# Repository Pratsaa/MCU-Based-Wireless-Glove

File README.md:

# MCU-Based Wireless Glove  

This project is a **wireless gesture-controlled glove** that streams **finger bends (flex sensors)** and **palm motion (IMU)** to a PC, where a Unity application animates a virtual hand in real time.  
- **STM32L031 MCU**: samples and processes sensor data.  
- **ESP32-WROOM**: handles wireless transmission via ESP-NOW.  
- **Python bridge**: ingests and calibrates data, then forwards it to Unity.  
- **Unity C# script**: applies finger and palm movements to a 3D hand model.  

👉 For detailed technical documentation (hardware schematics, PCB design, and system explanation), please see the [Docs/](./Docs) folder.  

---

## 📂 Repository Structure  

MCU-Based-Wireless-Glove/
│
├── Docs/ # Project documentation (ECE395 Final Report + notes)
├── pcb-files/ # PCB schematics, layouts, and related design files
├── src/ # Source code for firmware, PC bridge, and Unity listener
│ ├── stm32/ # STM32 firmware (ADC, IMU SPI, UART output)
│ ├── esp32/ # ESP32 firmware (ESP-NOW wireless bridge, optional IMU polling)
│ ├── python/ # PC-side scripts (serial ingest, calibration, TCP forward)
│ └── unity/ # Unity C# listener scripts (GloveReceiver.cs)
├── placeholder/ # Temporary / unused files (safe to ignore)
├── LICENSE # License information
└── README.md # Project overview (this file)

- **Docs/** – contains the final project report and supporting documents. Start here if you want to understand the full design.  
- **pcb-files/** – all hardware-related design files for the custom PCB.  
- **src/** – source code divided into:  
  - **stm32/** – firmware for STM32L031 MCU (flex sensor ADC, IMU via SPI, UART data framing).  
  - **esp32/** – firmware for ESP32 (wireless data forwarding using ESP-NOW, with optional IMU fallback).  
  - **python/** – PC bridge (`main.py` and helpers) that parses UART data, calibrates sensor values, and forwards JSON over TCP.  
  - **unity/** – Unity scripts (e.g., `GloveReceiver.cs`) that apply incoming data to animate a 3D hand model.  
- **placeholder/** – unused or staging area, not critical to the project.  

---

## ▶️ How It Works  

1. **Sensor acquisition**  
   - Flex sensors + op-amp circuits measure finger bends.  
   - IMU (ICM-20948) provides palm orientation and motion data.  
   - STM32 samples all signals and sends data over UART to the ESP32.  

2. **Wireless bridge**  
   - ESP32 transmits processed sensor data wirelessly to the PC via ESP-NOW.  

3. **PC bridge (Python)**  
   - Parses UART data, calibrates values, and forwards JSON packets over TCP.  

4. **Unity listener**  
   - Receives the data and animates a virtual hand in Unity with low latency.  

---

## 🛠️ Getting Started  

- Build and flash STM32 firmware (inside `src/`).  
- Flash ESP32 firmware (inside `src/`).  
- Run the Python script to ingest sensor data and forward to Unity.  
- Import the Unity C# script into your project to animate the hand.  

**Dependencies:**  
- STM32CubeIDE (or equivalent toolchain)  
- ESP-IDF for ESP32  
- Python 3.x with `pyserial`  
- Unity (2021 LTS or newer recommended)  

---

## 📖 Documentation  

Full documentation and project report can be found in [Docs/](./Docs). This includes:  
- Hardware schematics & PCB design decisions  
- Firmware architecture  
- Python/Unity pipeline  
- Performance metrics and improvements  

---

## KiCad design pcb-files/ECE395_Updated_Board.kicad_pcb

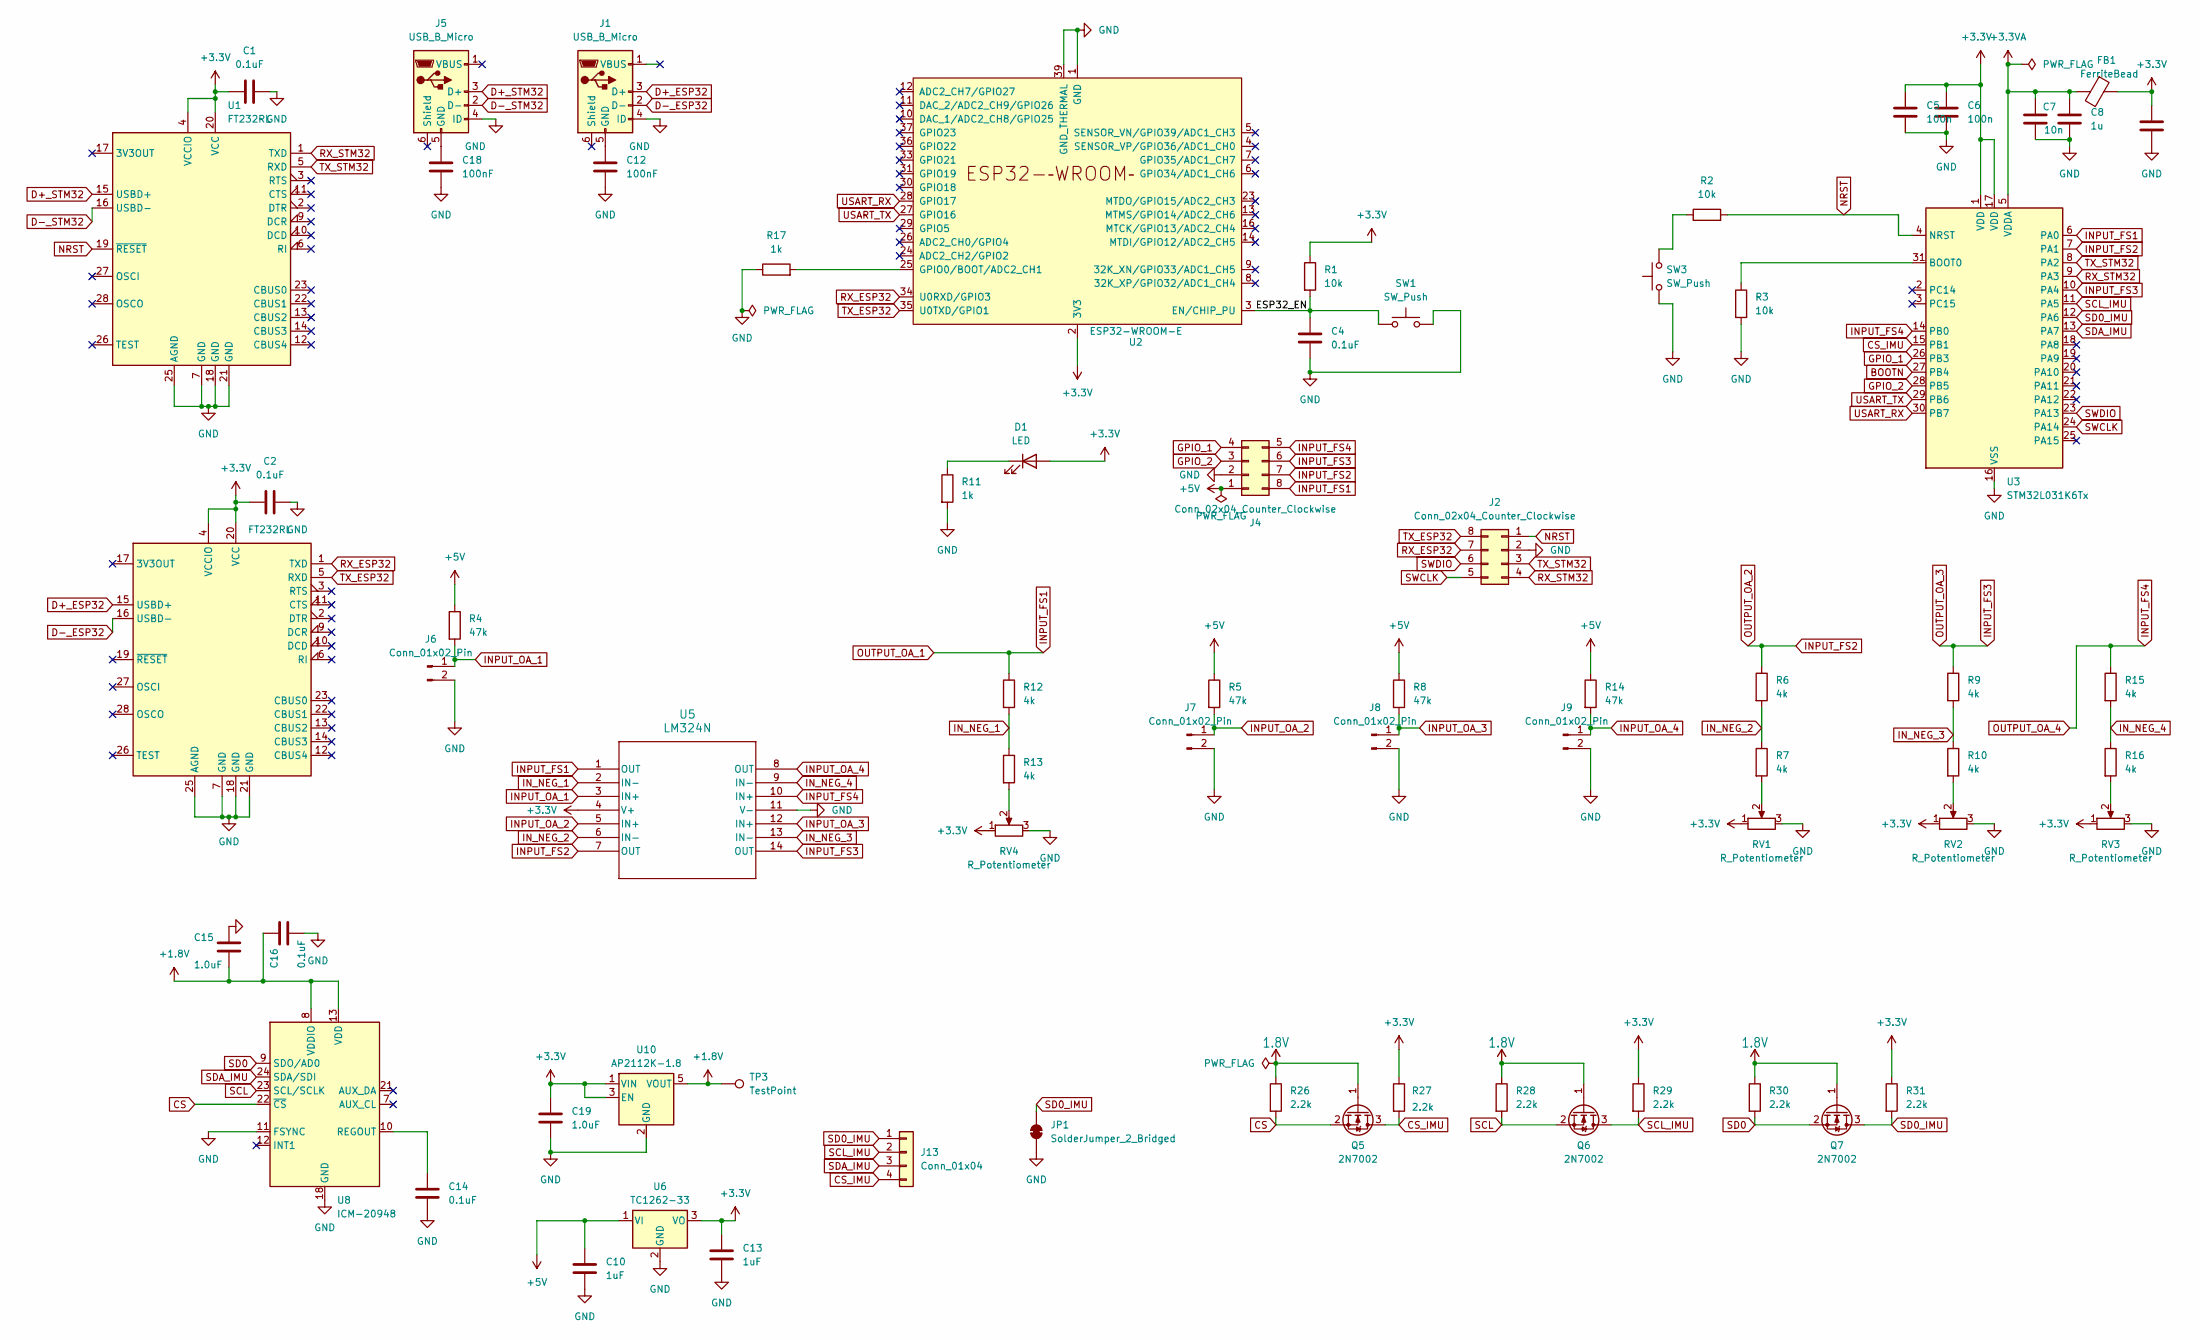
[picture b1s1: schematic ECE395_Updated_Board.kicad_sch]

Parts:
C1, C2, C4, C14, C16: 0.1uF; C_0805_2012Metric_Pad1.18x1.45mm_HandSolder
C5, C6: 100n; C_0805_2012Metric_Pad1.18x1.45mm_HandSolder
C7: 10n; C_0805_2012Metric_Pad1.18x1.45mm_HandSolder
C8, C9: 1u; C_0805_2012Metric_Pad1.18x1.45mm_HandSolder
C10, C13: 1uF; C_0805_2012Metric_Pad1.18x1.45mm_HandSolder
C12, C18: 100nF; C_0805_2012Metric_Pad1.18x1.45mm_HandSolder
C15, C19: 1.0uF; C_0805_2012Metric_Pad1.18x1.45mm_HandSolder
D1: LED; LED_0805_2012Metric_Pad1.15x1.40mm_HandSolder
FB1: FerriteBead; L_0805_2012Metric_Pad1.15x1.40mm_HandSolder
J1, J5: USB_B_Micro; USB_Micro-B_Amphenol_10118194-0001LF_Horizontal
J2, J4: Conn_02x04_Counter_Clockwise; PinHeader_2x04_P2.54mm_Vertical
J6, J7, J8, J9: Conn_01x02_Pin; PinHeader_1x02_P2.54mm_Vertical
J13: Conn_01x04; PinHeader_1x04_P2.54mm_Vertical
JP1: SolderJumper_2_Bridged; SolderJumper-2_P1.3mm_Bridged_RoundedPad1.0x1.5mm
Q5, Q6, Q7: 2N7002; SOT-23
R1, R2, R3: 10k; R_0805_2012Metric_Pad1.20x1.40mm_HandSolder
R4, R5, R8, R14: 47k; R_0805_2012Metric_Pad1.20x1.40mm_HandSolder
R6, R7, R9, R10, R12, R13, R15, R16: 4k; R_0805_2012Metric_Pad1.20x1.40mm_HandSolder
R11, R17: 1k; R_0805_2012Metric_Pad1.20x1.40mm_HandSolder
R26, R27, R28, R29, R30, R31: 2.2k; R_0805_2012Metric_Pad1.20x1.40mm_HandSolder
RV1, RV2, RV3, RV4: R_Potentiometer; Potentiometer_Bourns_3296W_Vertical
SW1, SW3: SW_Push; SW_PUSH_6mm
TP3: TestPoint; TestPoint_2Pads_Pitch2.54mm_Drill0.8mm
U1, U4: FT232RL; SSOP-28_5.3x10.2mm_P0.65mm
U2: ESP32-WROOM-E; ESP32­WROOM­32E_EXP
U3: STM32L031K6Tx; LQFP-32_7x7mm_P0.8mm
U5: LM324N; DIP-14_STM
U6: TC1262-33; SOT-223
U8: ICM-20948; InvenSense_QFN-24_3x3mm_P0.4mm
U10: AP2112K-1.8; SOT-23-5

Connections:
1.8V: Q5.1 (G), Q6.1 (G), Q7.1 (G), R26.1, R28.1, R30.1
+1.8V: C15.2, C16.1, TP3.1, U8.8 (VDDIO), U8.13 (VDD), U10.5 (VOUT)
+3.3V: C1.1, C2.1, C5.1, C6.1, C9.1, C13.2, C19.1, D1.2 (A), FB1.1, R1.1, R27.1, R29.1, R31.1, RV1.1, RV2.1, RV3.1, RV4.1, U1.4 (VCCIO), U1.20 (VCC), U2.2 (3V3), U3.1 (VDD), U3.17 (VDD), U4.4 (VCCIO), U4.20 (VCC), U5.4 (V+), U6.3 (VO), U10.1 (VIN), U10.3 (EN); also elsewhere on the board
+3.3VA: C7.1, C8.1, FB1.2, U3.5 (VDDA)
+5V: C10.2, J4.1, R4.1, R5.1, R8.1, R14.1, U6.1 (VI)
/ESP32_EN: C4.1, R1.2, SW1.1, U2.3 (EN/CHIP_PU)
BOOTN: U3.27 (PB4)
CS: Q5.2 (S), R26.2, U8.22 (~CS)
CS_IMU: J13.4, Q5.3 (D), R27.2, U3.15 (PB1)
D+_ESP32: J1.3 (D+), U4.15 (USBD+)
D+_STM32: J5.3 (D+), U1.15 (USBD+)
D-_ESP32: J1.2 (D-), U4.16 (USBD-)
D-_STM32: J5.2 (D-), U1.16 (USBD-)
GND: C1.2, C2.2, C4.2, C5.2, C6.2, C7.2, C8.2, C9.2, C10.1, C12.2, C13.1, C14.2, C15.1, C16.2, C18.2, C19.2, J1.4 (ID), J2.2, J4.2, J5.4 (ID), J6.2, J7.2, J8.2, J9.2, JP1.1 (A), R3.2, R11.2, R17.1, RV1.3, RV2.3, RV3.3, RV4.3, SW1.2, SW3.1, U1.7 (GND), U1.18 (GND), U1.21 (GND), U1.25 (AGND), U2.1 (GND), U2.15 (GND), U2.38 (GND), U2.39 (GND_THERMAL), U3.16 (VSS), U3.32 (VSS), U4.7 (GND), U4.18 (GND), U4.21 (GND), U4.25 (AGND), U5.11 (V-), U6.2 (GND), U8.11 (FSYNC), U8.18 (GND), U8.20 (GND), U10.2 (GND)
GPIO_1: J4.4, U3.26 (PB3)
GPIO_2: J4.3, U3.28 (PB5)
INPUT_FS1: J4.8, R12.1, U3.6 (PA0), U5.1 (OUT)
INPUT_FS2: J4.7, R6.1, U3.7 (PA1), U5.7 (OUT)
INPUT_FS3: J4.6, R9.1, U3.10 (PA4), U5.14 (OUT)
INPUT_FS4: J4.5, R15.1, U3.14 (PB0), U5.10 (IN+)
INPUT_OA_1: J6.1, R4.2, U5.3 (IN+)
INPUT_OA_2: J7.1, R5.2, U5.5 (IN+)
INPUT_OA_3: J8.1, R8.2, U5.12 (IN+)
INPUT_OA_4: J9.1, R14.2, U5.8 (OUT)
IN_NEG_1: R12.2, R13.1, U5.2 (IN-)
IN_NEG_2: R6.2, R7.1, U5.6 (IN-)
IN_NEG_3: R9.2, R10.1, U5.13 (IN-)
IN_NEG_4: R15.2, R16.1, U5.9 (IN-)
NRST: J2.1, R2.2, U1.19 (~RESET), U3.4 (NRST)
unnamed: D1.1 (K), R11.1
unnamed: C12.1, J1.5 (GND)
unnamed: C18.1, J5.5 (GND)
unnamed: R2.1, SW3.2
unnamed: R7.2, RV1.2
unnamed: R10.2, RV2.2
unnamed: R13.2, RV4.2
unnamed: R16.2, RV3.2
unnamed 37: R17.2, U2.25 (GPIO0/BOOT/ADC2_CH1); also elsewhere on the board
unnamed: R3.1, U3.31 (BOOT0)
unnamed: C14.1, U8.10 (REGOUT)
RX_ESP32: J2.7, U2.34 (U0RXD/GPIO3), U4.1 (TXD)
RX_STM32: J2.4, U1.1 (TXD), U3.9 (PA3)
SCL: Q6.2 (S), R28.2, U8.23 (SCL/SCLK)
SCL_IMU: J13.2, Q6.3 (D), R29.2, U3.11 (PA5)
SD0: Q7.2 (S), R30.2, U8.9 (SDO/AD0)
SD0_IMU: J13.1, JP1.2 (B), Q7.3 (D), R31.2, U3.12 (PA6)
SDA_IMU: J13.3, U3.13 (PA7), U8.24 (SDA/SDI)
SWCLK: J2.5, U3.24 (PA14)
SWDIO: J2.6, U3.23 (PA13)
TX_ESP32: J2.8, U2.35 (U0TXD/GPIO1), U4.5 (RXD)
TX_STM32: J2.3, U1.5 (RXD), U3.8 (PA2)
USART_RX: U2.28 (GPIO17), U3.30 (PB7)
USART_TX: U2.27 (GPIO16), U3.29 (PB6)

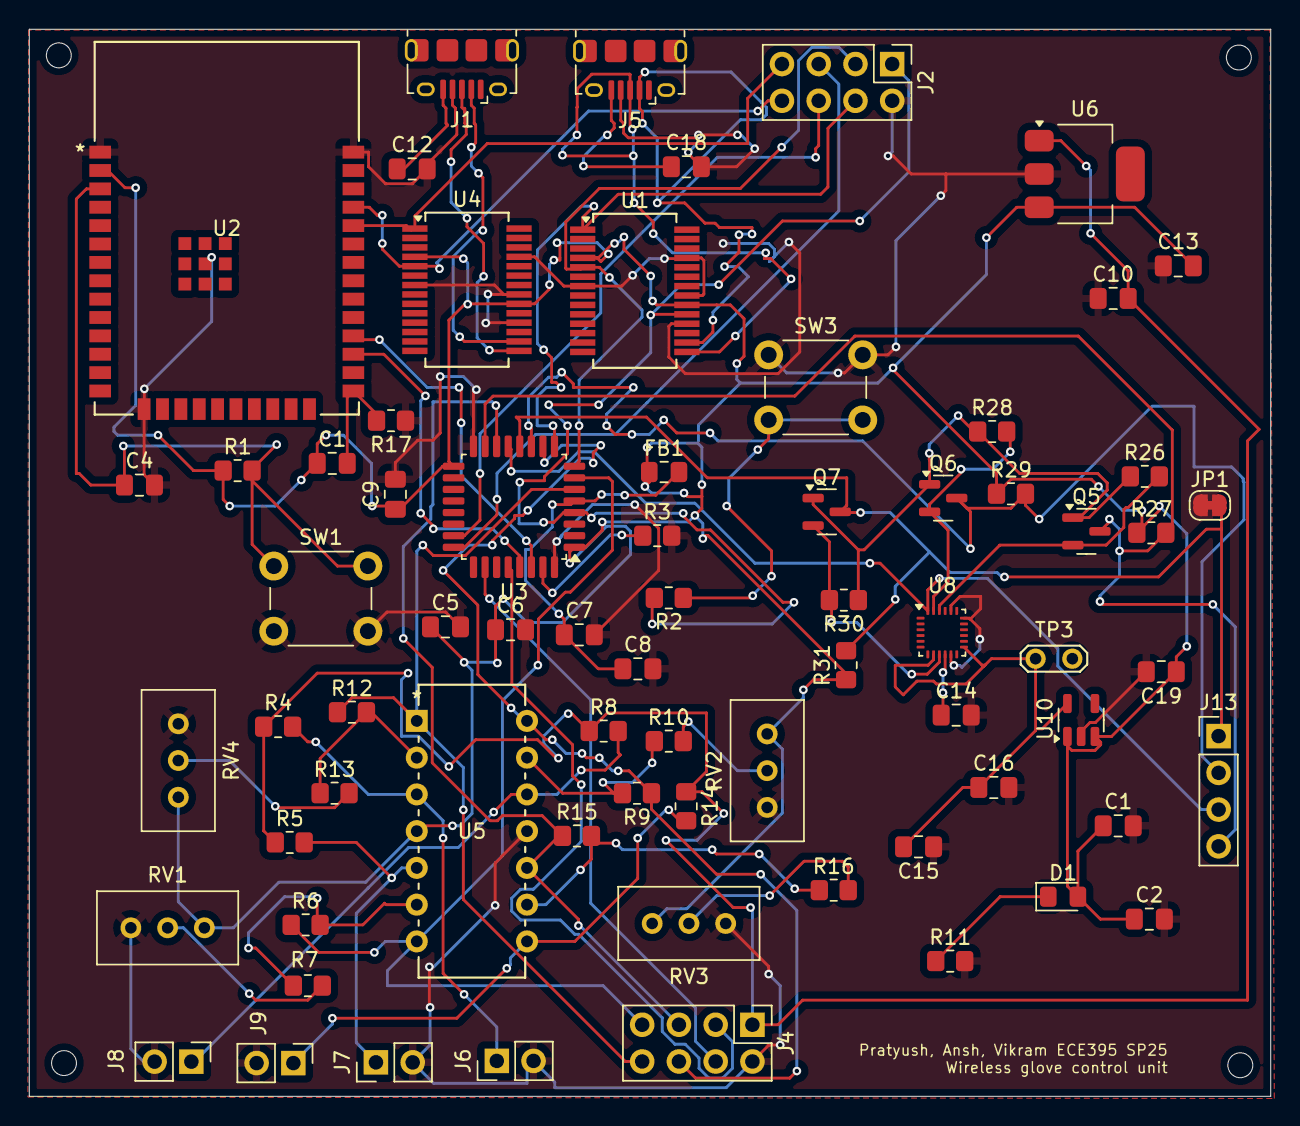
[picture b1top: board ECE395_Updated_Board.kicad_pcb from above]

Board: 2 copper layers, 85.8 x 73.8 mm, 70 parts (0 on the bottom side), 52 nets.

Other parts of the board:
C1#2: 0.1uF; C_0805_2012Metric_Pad1.18x1.45mm_HandSolder

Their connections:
+3.3V: C1#2.1; also elsewhere on the board
unnamed 37: C1#2.2; also elsewhere on the board

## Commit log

2025-08-18 Initial commit: wireless MCU glove
2025-08-21 Create placeholder
2025-08-21 Created sender folder
2025-08-21 Added all the wireless bridge (python) files used
2025-08-21 Renamed folder to wireless-bridge-files
2025-08-21 Update and renamed folder
2025-08-21 Updating my repo
2025-08-21 Updated all the wireless bridge (python) files
2025-08-21 Updating this repo
2025-08-30 latest commit of control unit supporting files
2025-08-30 latest commit
2025-08-30 latest_commit
2025-08-30 latest commit of the main control unit code
2025-08-30 commiting latest (supporting) code files
2025-08-30 latest pcb files
2025-08-30 latest commit (docs)
